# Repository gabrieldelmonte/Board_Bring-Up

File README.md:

# Board Bring-Up Project

A microcontroller-based embedded system project featuring real-time monitoring, alarm management, and multi-language support using the PIC18F4550 microcontroller.

## Project Overview

This project implements a comprehensive board bring-up system that combines multiple peripherals and sensors to create a monitoring and control system. The system features a state machine-based architecture with real-time clock functionality, analog sensor monitoring, alarm management, and a user-friendly LCD interface.

## Features

### Core Functionality
- **Real-Time Clock (RTC)**: DS1307-based timekeeping with hour, minute, and second setting
- **Analog Monitoring**: ADC-based sensor reading with configurable alarm thresholds
- **Alarm System**: Dual-level alarm monitoring (high/low thresholds) with visual indicators
- **Multi-Language Support**: Interface available in 6 different languages
- **State Machine Architecture**: Robust navigation system between different operational modes

### Hardware Peripherals
- **LCD Display**: 16-character display for system information and menus
- **LED Control**: Visual feedback and alarm indication system
- **Button Interface**: Navigation and parameter adjustment controls
- **I2C Communication**: For RTC and DAC communication
- **PWM Output**: Pulse width modulation for analog output control
- **Serial Communication**: UART interface for debugging and external communication
- **DAC Output**: MCP4725-based digital-to-analog conversion

### System States
- **Menu**: Main navigation interface
- **Alarm Configuration**: Set high and low alarm thresholds
- **Language Selection**: Choose from 6 available languages
- **Time Setting**: Configure hours, minutes, and seconds
- **Warning Mode**: Alert state when alarm conditions are triggered

## Hardware Requirements

### Microcontroller
- **PIC18F4550** microcontroller
- **20 MHz** crystal oscillator
- Power supply and basic support components

### Peripherals
- **DS1307** Real-Time Clock module
- **MCP4725** Digital-to-Analog Converter
- **16x2 LCD Display** with HD44780 controller
- **LEDs** for status indication
- **Push buttons** for user interface
- **Analog sensor** (connected to ADC channel 0)

### Development Tools
- MPLAB X IDE or compatible PIC development environment
- XC8 compiler for PIC18 family
- Programmer/debugger (PICkit, ICD, etc.)

## Project Structure

```
Board_Bring-Up/
├── src/
│   ├── main.c              # Main application entry point
│   └── code/
│       ├── ADC.c           # Analog-to-Digital Converter functions
│       ├── button.c        # Button handling and debouncing
│       ├── DAC_MCP4725.c   # MCP4725 DAC communication
│       ├── delay.c         # Timing and delay functions
│       ├── event.c         # Event handling and system events
│       ├── I2C.c           # I2C communication protocol
│       ├── LCD.c           # LCD display control functions
│       ├── LED.c           # LED control and patterns
│       ├── output.c        # Output formatting and display
│       ├── PWM.c           # Pulse Width Modulation control
│       ├── RTC_DS1307.c    # Real-Time Clock functions
│       ├── serial.c        # UART serial communication
│       ├── stateMachine.c  # Main state machine implementation
│       ├── variables.c     # Global variable management
│       └── headers/        # Header files for all modules
├── hardware/               # KiCad PCB design files
├── diagrams/               # System architecture diagrams
└── docs/                   # Project documentation
```

## Getting Started

### Prerequisites
1. MPLAB X IDE installed
2. XC8 compiler for PIC18 family
3. PIC programmer/debugger
4. Assembled hardware board or prototyping setup

### Building the Project
1. Clone this repository:
   ```bash
   git clone https://github.com/your-username/Board_Bring-Up.git
   cd Board_Bring-Up
   ```

2. Open the project in MPLAB X IDE

3. Configure the project settings:
   - Select PIC18F4550 as target device
   - Set XC8 as the compiler
   - Configure programmer/debugger

4. Build the project:
   - Click "Build" or use Ctrl+F11
   - Resolve any compilation errors

5. Program the microcontroller:
   - Connect your programmer
   - Click "Make and Program Device"

### Hardware Setup
1. Connect the LCD display to PORTD and control pins (RA2, RA3)
2. Wire the DS1307 RTC to the I2C bus (RC3/SCL, RC4/SDA)
3. Connect analog sensor to AN0 (RA0)
4. Wire push buttons for navigation
5. Connect LEDs for status indication
6. Ensure proper power supply (5V for PIC18F4550)

## Usage

### Navigation
- **Base Button**: Return to main menu from any state
- **Left/Right Buttons**: Navigate between menu options
- **Up/Down Buttons**: Adjust values in configuration modes

### Setting Alarms
1. Navigate to alarm configuration states
2. Use up/down buttons to adjust high and low thresholds
3. System will trigger warnings when sensor readings exceed limits

### Time Configuration
1. Access time setting modes through menu navigation
2. Adjust hours, minutes, and seconds individually
3. Changes are automatically saved to RTC

### Language Selection
- Navigate to language menu
- Choose from 6 available language options
- Interface will update to selected language

## Configuration

### System Parameters
Key configuration options in `defines.h`:
- `FREQ`: System frequency (20 MHz)
- `NUMBER_LANGUAGES`: Available languages (6)
- `MAX_ADC_VALUE`: Maximum ADC reading (1000)
- `MIN_ADC_VALUE`: Minimum ADC reading (0)

### Pin Assignments
- **LCD Data**: PORTD (RD0-RD7)
- **LCD Control**: RA2 (RS), RA3 (EN)
- **I2C**: RC3 (SCL), RC4 (SDA)
- **ADC Input**: RA0 (AN0)
- **LED Outputs**: Configurable in LED.c

## Additional Resources

- [PIC18F4550 Datasheet](https://www.microchip.com/en-us/product/PIC18F4550)
- [DS1307 RTC Datasheet](https://datasheets.maximintegrated.com/en/ds/DS1307.pdf)
- [MCP4725 DAC Datasheet](https://ww1.microchip.com/downloads/en/DeviceDoc/22039d.pdf)
- PCB design files are available in the `hardware/` directory

## License

This project is licensed under the terms specified in the LICENSE file.

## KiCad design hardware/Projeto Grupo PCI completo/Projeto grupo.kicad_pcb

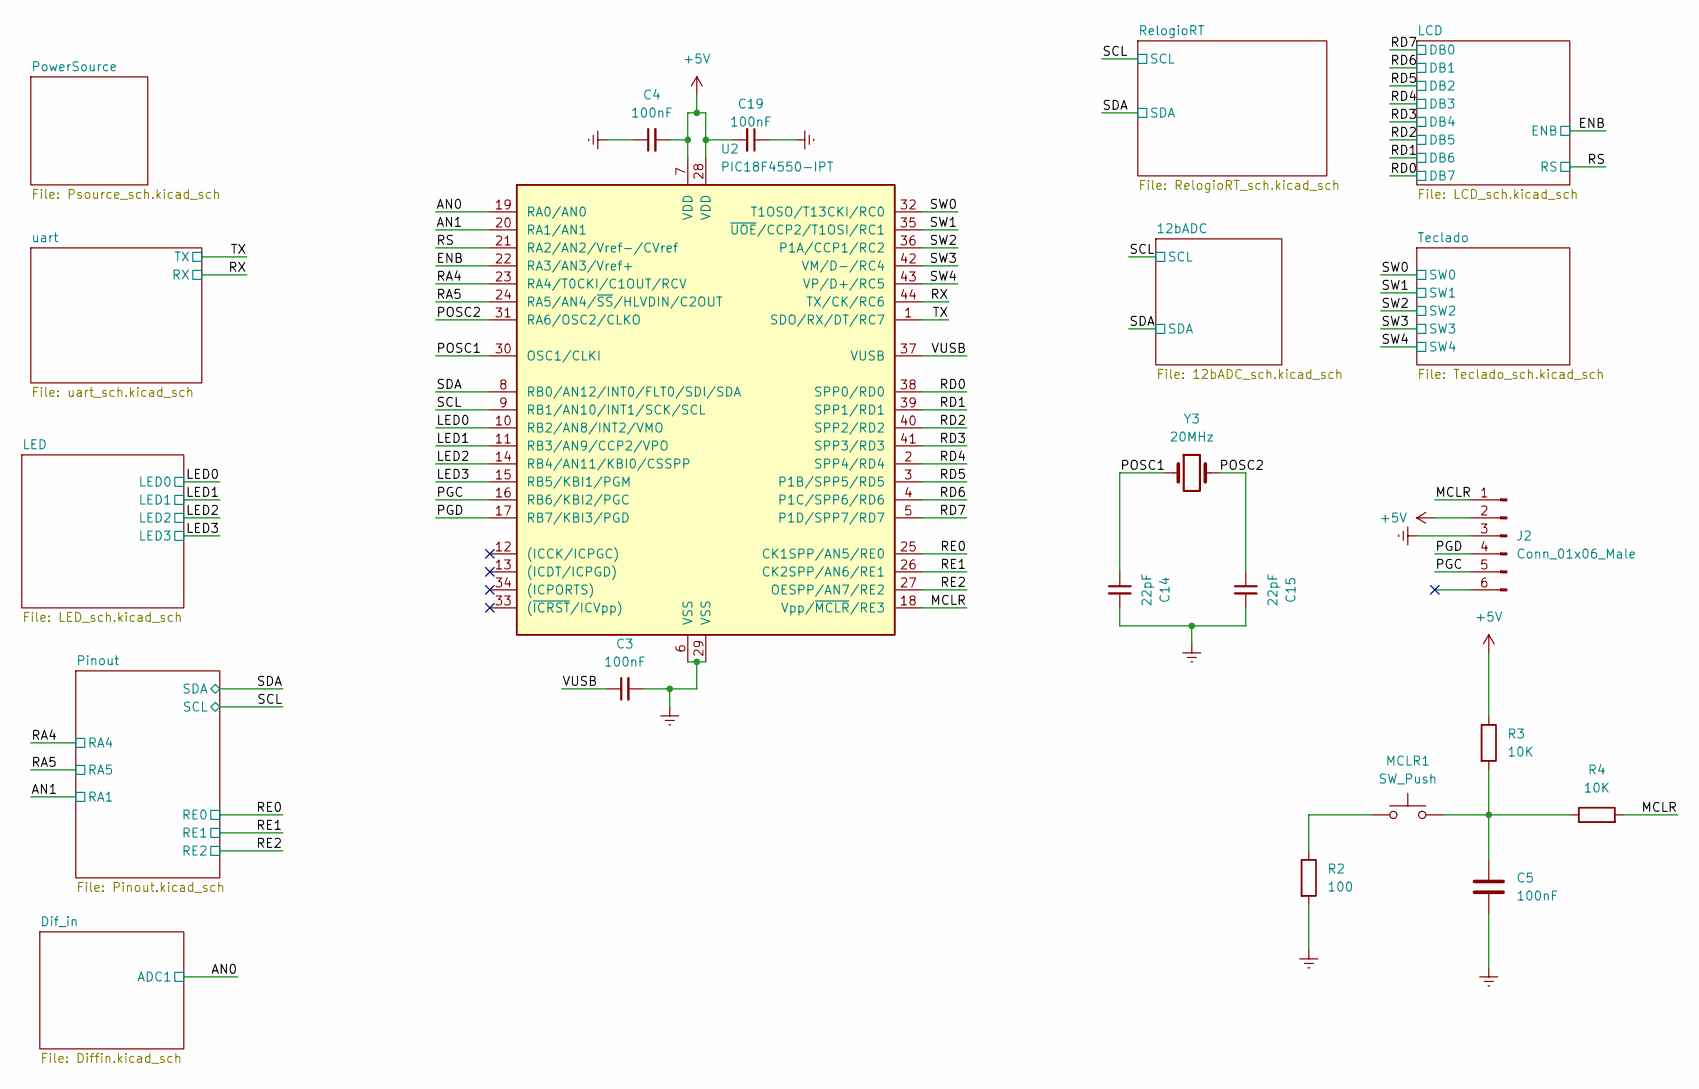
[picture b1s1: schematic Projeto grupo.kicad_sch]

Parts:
C3, C4, C5, C19: 100nF; C_0805_2012Metric
C14, C15: 22pF; C_0805_2012Metric
J2: Conn_01x06_Male; PinHeader_1x06_P2.54mm_Vertical
MCLR1: SW_Push; SW_PUSH_6mm
R2: 100; R_0805_2012Metric
R3, R4: 10K; R_0805_2012Metric
U2: PIC18F4550-IPT; TQFP-44_10x10mm_P0.8mm
Y3: 20MHz; Crystal_HC49-4H_Vertical

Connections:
+5V: C4.2, C19.2, J2.2, R3.1, U2.7 (VDD), U2.28 (VDD); also elsewhere on the board
/AN0: U2.19 (RA0/AN0); also elsewhere on the board
/AN1: U2.20 (RA1/AN1); also elsewhere on the board
/ENB: U2.22 (RA3/AN3/Vref+); also elsewhere on the board
/LED0: U2.10 (RB2/AN8/INT2/VMO); also elsewhere on the board
/LED1: U2.11 (RB3/AN9/CCP2/VPO); also elsewhere on the board
/LED2: U2.14 (RB4/AN11/KBI0/CSSPP); also elsewhere on the board
/LED3: U2.15 (RB5/KBI1/PGM); also elsewhere on the board
/MCLR: J2.1, R4.2, U2.18 (Vpp/~MCLR/RE3)
/PGC: J2.5, U2.16 (RB6/KBI2/PGC)
/PGD: J2.4, U2.17 (RB7/KBI3/PGD)
/POSC1: C14.1, U2.30 (OSC1/CLKI), Y3.1
/POSC2: C15.1, U2.31 (RA6/OSC2/CLKO), Y3.2
/RA4: U2.23 (RA4/T0CKI/C1OUT/RCV); also elsewhere on the board
/RA5: U2.24 (RA5/AN4/~SS/HLVDIN/C2OUT); also elsewhere on the board
/RD0: U2.38 (SPP0/RD0); also elsewhere on the board
/RD1: U2.39 (SPP1/RD1); also elsewhere on the board
/RD2: U2.40 (SPP2/RD2); also elsewhere on the board
/RD3: U2.41 (SPP3/RD3); also elsewhere on the board
/RD4: U2.2 (SPP4/RD4); also elsewhere on the board
/RD5: U2.3 (P1B/SPP5/RD5); also elsewhere on the board
/RD6: U2.4 (P1C/SPP6/RD6); also elsewhere on the board
/RD7: U2.5 (P1D/SPP7/RD7); also elsewhere on the board
/RE0: U2.25 (CK1SPP/AN5/RE0); also elsewhere on the board
/RE1: U2.26 (CK2SPP/AN6/RE1); also elsewhere on the board
/RE2: U2.27 (OESPP/AN7/RE2); also elsewhere on the board
/RS: U2.21 (RA2/AN2/Vref-/CVref); also elsewhere on the board
/RX: U2.44 (TX/CK/RC6); also elsewhere on the board
/SCL: U2.9 (RB1/AN10/INT1/SCK/SCL); also elsewhere on the board
/SDA: U2.8 (RB0/AN12/INT0/FLT0/SDI/SDA); also elsewhere on the board
/SW0: U2.32 (T1OSO/T13CKI/RC0); also elsewhere on the board
/SW1: U2.35 (~UOE/CCP2/T1OSI/RC1); also elsewhere on the board
/SW2: U2.36 (P1A/CCP1/RC2); also elsewhere on the board
/SW3: U2.42 (VM/D-/RC4); also elsewhere on the board
/SW4: U2.43 (VP/D+/RC5); also elsewhere on the board
/TX: U2.1 (SDO/RX/DT/RC7); also elsewhere on the board
/VUSB: C3.1, U2.37 (VUSB)
Earth: C3.2, C4.1, C5.2, C14.2, C15.2, C19.1, J2.3, R2.2, U2.6 (VSS), U2.29 (VSS); also elsewhere on the board
unnamed 39: C5.1, MCLR1.2, R3.2, R4.1; also elsewhere on the board
unnamed 60: MCLR1.1, R2.1; also elsewhere on the board

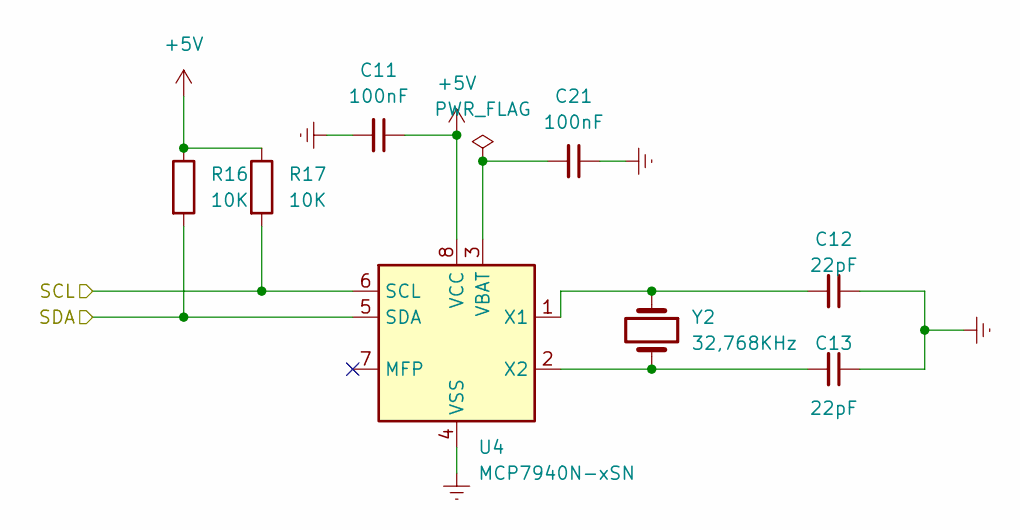
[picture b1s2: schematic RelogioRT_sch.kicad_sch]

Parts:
C11, C21: 100nF; C_0805_2012Metric
C12, C13: 22pF; C_0805_2012Metric
R16, R17: 10K; R_0805_2012Metric
U4: MCP7940N-xSN
Y2: 32,768KHz; AB38T32768KHZ

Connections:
+5V: C11.1, R16.1, R17.1, U4.8 (VCC); also elsewhere on the board
/SCL: R17.2, U4.6 (SCL); also elsewhere on the board
/SDA: R16.2, U4.5 (SDA); also elsewhere on the board
Earth: C11.2, C12.1, C13.1, C21.1, U4.4 (VSS); also elsewhere on the board
unnamed: C12.2, U4.1 (X1), Y2.1
unnamed: C13.2, U4.2 (X2), Y2.2
unnamed: C21.2, U4.3 (VBAT)

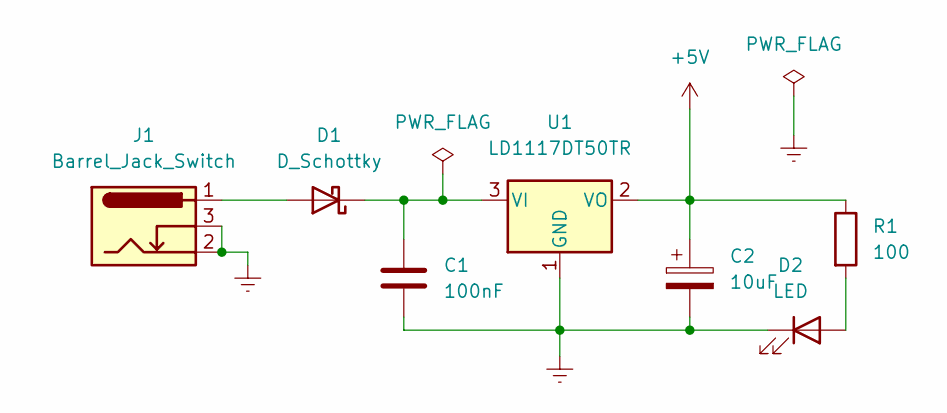
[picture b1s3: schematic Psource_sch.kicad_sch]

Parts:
C1: 100nF; C_0805_2012Metric
C2: 10uF; CP_EIA-3216-12_Kemet-S
D1: D_Schottky; D_SOD-123
D2: LED; LED_1206_3216Metric_Pad1.42x1.75mm_HandSolder
J1: Barrel_Jack_Switch; BarrelJack_Horizontal
R1: 100; R_0805_2012Metric
U1: LD1117DT50TR; ATPAK-2

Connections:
+5V: C2.1, R1.1, U1.2 (VO); also elsewhere on the board
Earth: C1.2, C2.2, D2.1 (K), J1.2, J1.3, U1.1 (GND); also elsewhere on the board
unnamed: C1.1, D1.1 (K), U1.3 (VI)
unnamed: D1.2 (A), J1.1
unnamed: D2.2 (A), R1.2

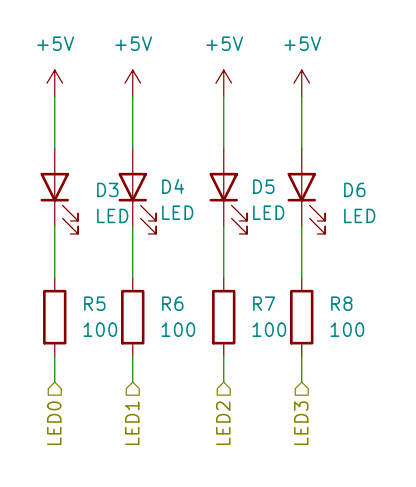
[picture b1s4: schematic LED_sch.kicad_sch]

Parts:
D3, D4, D5, D6: LED; LED_1206_3216Metric_Pad1.42x1.75mm_HandSolder
R5, R6, R7, R8: 100; R_0805_2012Metric

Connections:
+5V: D3.2 (A), D4.2 (A), D5.2 (A), D6.2 (A); also elsewhere on the board
/LED0: R5.2; also elsewhere on the board
/LED1: R6.2; also elsewhere on the board
/LED2: R7.2; also elsewhere on the board
/LED3: R8.2; also elsewhere on the board
unnamed: D3.1 (K), R5.1
unnamed: D4.1 (K), R6.1
unnamed: D5.1 (K), R7.1
unnamed: D6.1 (K), R8.1

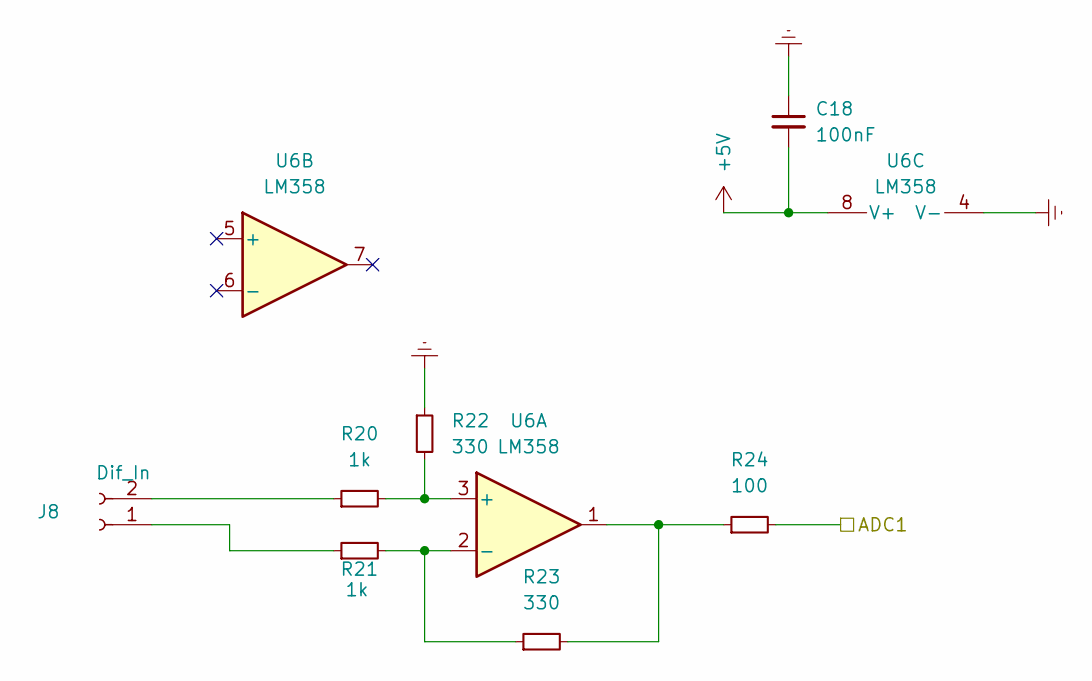
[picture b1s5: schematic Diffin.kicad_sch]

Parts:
C18: 100nF; C_0805_2012Metric
J8: Dif_In; On_Shore_Technology-OSTTA024163-0-0-MFG
R20, R21: 1k; R_0805_2012Metric
R22, R23: 330; R_0805_2012Metric
R24: 100; R_0805_2012Metric
U6: LM358

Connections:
+5V: C18.2, U6.8 (V+); also elsewhere on the board
/AN0: R24.2; also elsewhere on the board
Earth: C18.1, R22.1, U6.4 (V-); also elsewhere on the board
unnamed: J8.1, R21.1
unnamed: J8.2, R20.1
unnamed: R20.2, R22.2, U6.3 (+)
unnamed: R21.2, R23.1, U6.2 (-)
unnamed: R23.2, R24.1, U6.1

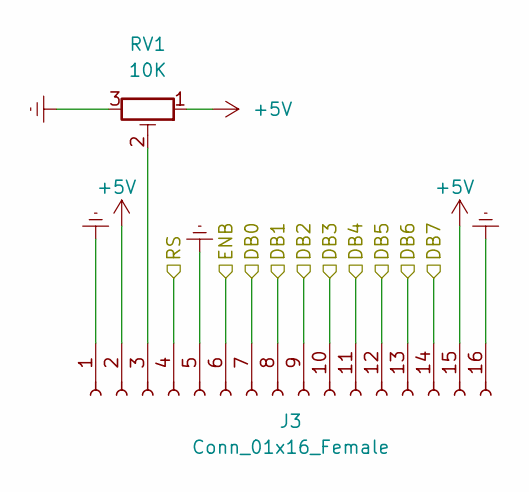
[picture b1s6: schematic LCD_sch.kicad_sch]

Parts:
J3: Conn_01x16_Female; PinSocket_1x16_P2.54mm_Vertical
RV1: 10K; Potentiometer_Bourns_3296W_Vertical

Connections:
+5V: J3.2, J3.15, RV1.1; also elsewhere on the board
/ENB: J3.6; also elsewhere on the board
/RD0: J3.14; also elsewhere on the board
/RD1: J3.13; also elsewhere on the board
/RD2: J3.12; also elsewhere on the board
/RD3: J3.11; also elsewhere on the board
/RD4: J3.10; also elsewhere on the board
/RD5: J3.9; also elsewhere on the board
/RD6: J3.8; also elsewhere on the board
/RD7: J3.7; also elsewhere on the board
/RS: J3.4; also elsewhere on the board
Earth: J3.1, J3.5, J3.16, RV1.3; also elsewhere on the board
unnamed: J3.3, RV1.2

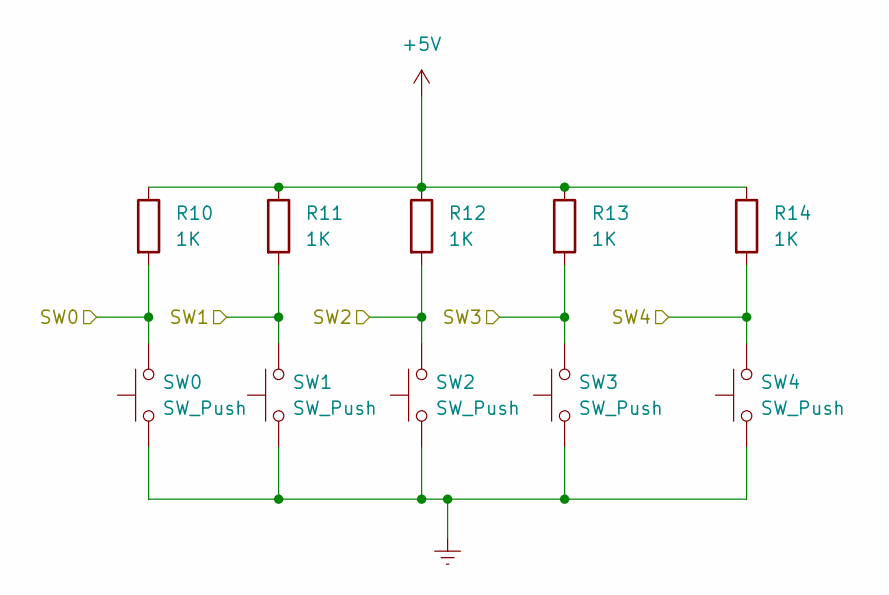
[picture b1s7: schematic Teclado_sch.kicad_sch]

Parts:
R10, R11, R12, R13, R14: 1K; R_0805_2012Metric
SW0, SW1, SW2, SW3, SW4: SW_Push; SW_PUSH_6mm

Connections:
+5V: R10.1, R11.1, R12.1, R13.1, R14.1; also elsewhere on the board
/SW0: R10.2, SW0.2; also elsewhere on the board
/SW1: R11.2, SW1.2; also elsewhere on the board
/SW2: R12.2, SW2.2; also elsewhere on the board
/SW3: R13.2, SW3.2; also elsewhere on the board
/SW4: R14.2, SW4.2; also elsewhere on the board
Earth: SW0.1, SW1.1, SW2.1, SW3.1, SW4.1; also elsewhere on the board

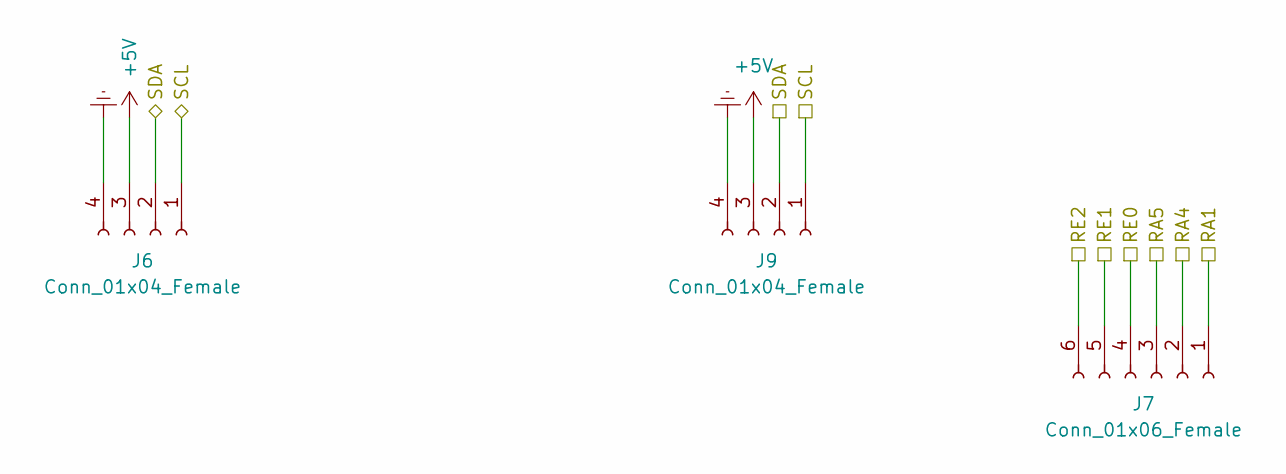
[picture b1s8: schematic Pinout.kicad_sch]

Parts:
J6, J9: Conn_01x04_Female; PinSocket_1x04_P2.54mm_Vertical
J7: Conn_01x06_Female; PinSocket_1x06_P2.54mm_Vertical

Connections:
+5V: J6.3, J9.3; also elsewhere on the board
/AN1: J7.1; also elsewhere on the board
/RA4: J7.2; also elsewhere on the board
/RA5: J7.3; also elsewhere on the board
/RE0: J7.4; also elsewhere on the board
/RE1: J7.5; also elsewhere on the board
/RE2: J7.6; also elsewhere on the board
/SCL: J6.1, J9.1; also elsewhere on the board
/SDA: J6.2, J9.2; also elsewhere on the board
Earth: J6.4, J9.4; also elsewhere on the board

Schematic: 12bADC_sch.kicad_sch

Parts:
C16: 100nF; C_0805_2012Metric
C17: 10uF; CP_EIA-3216-12_Kemet-S
J5: adcout; On_Shore_Technology-OSTTA024163-0-0-MFG
R15: 100; R_0805_2012Metric
U5: MCP4725A0T-E/CH; SOT-23-6

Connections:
+5V: C16.2, C17.1, U5.3 (VDD); also elsewhere on the board
/SCL: U5.5 (SCL); also elsewhere on the board
/SDA: U5.4 (SDA); also elsewhere on the board
Earth: C16.1, C17.2, J5.2, U5.2 (VSS), U5.6 (A0); also elsewhere on the board
unnamed: J5.1, R15.2
unnamed: R15.1, U5.1 (VOUT)

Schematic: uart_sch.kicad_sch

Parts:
C6, C7: 22pF; C_0805_2012Metric
C8, C9, C20: 100nF; C_0805_2012Metric
C10: 220nF; C_0805_2012Metric
J4: USB_A; USB_B_Lumberg_2411_02_Horizontal
R9: 10K; R_0805_2012Metric
U3: MCP2200-I-SO; SOIC-20W_7.5x12.8mm_P1.27mm
Y1: 12MHz; Crystal_HC49-4H_Vertical

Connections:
+5V: C9.2, R9.1, U3.1 (VDD); also elsewhere on the board
/RX: U3.12 (RX); also elsewhere on the board
/TX: U3.10 (TX); also elsewhere on the board
Earth: C6.2, C7.2, C8.1, C9.1, C10.2, C20.1, J4.4 (GND), U3.20 (VSS); also elsewhere on the board
unnamed: C6.1, U3.2 (OSC1), Y1.2
unnamed: C7.1, U3.3 (OSC2), Y1.1
unnamed: C8.2, R9.2, U3.4 (RST)
unnamed: C10.1, U3.17 (V_USB)
unnamed: C20.2, J4.1 (VBUS)
unnamed: J4.2 (D-), U3.18 (D-)
unnamed: J4.3 (D+), U3.19 (D+)

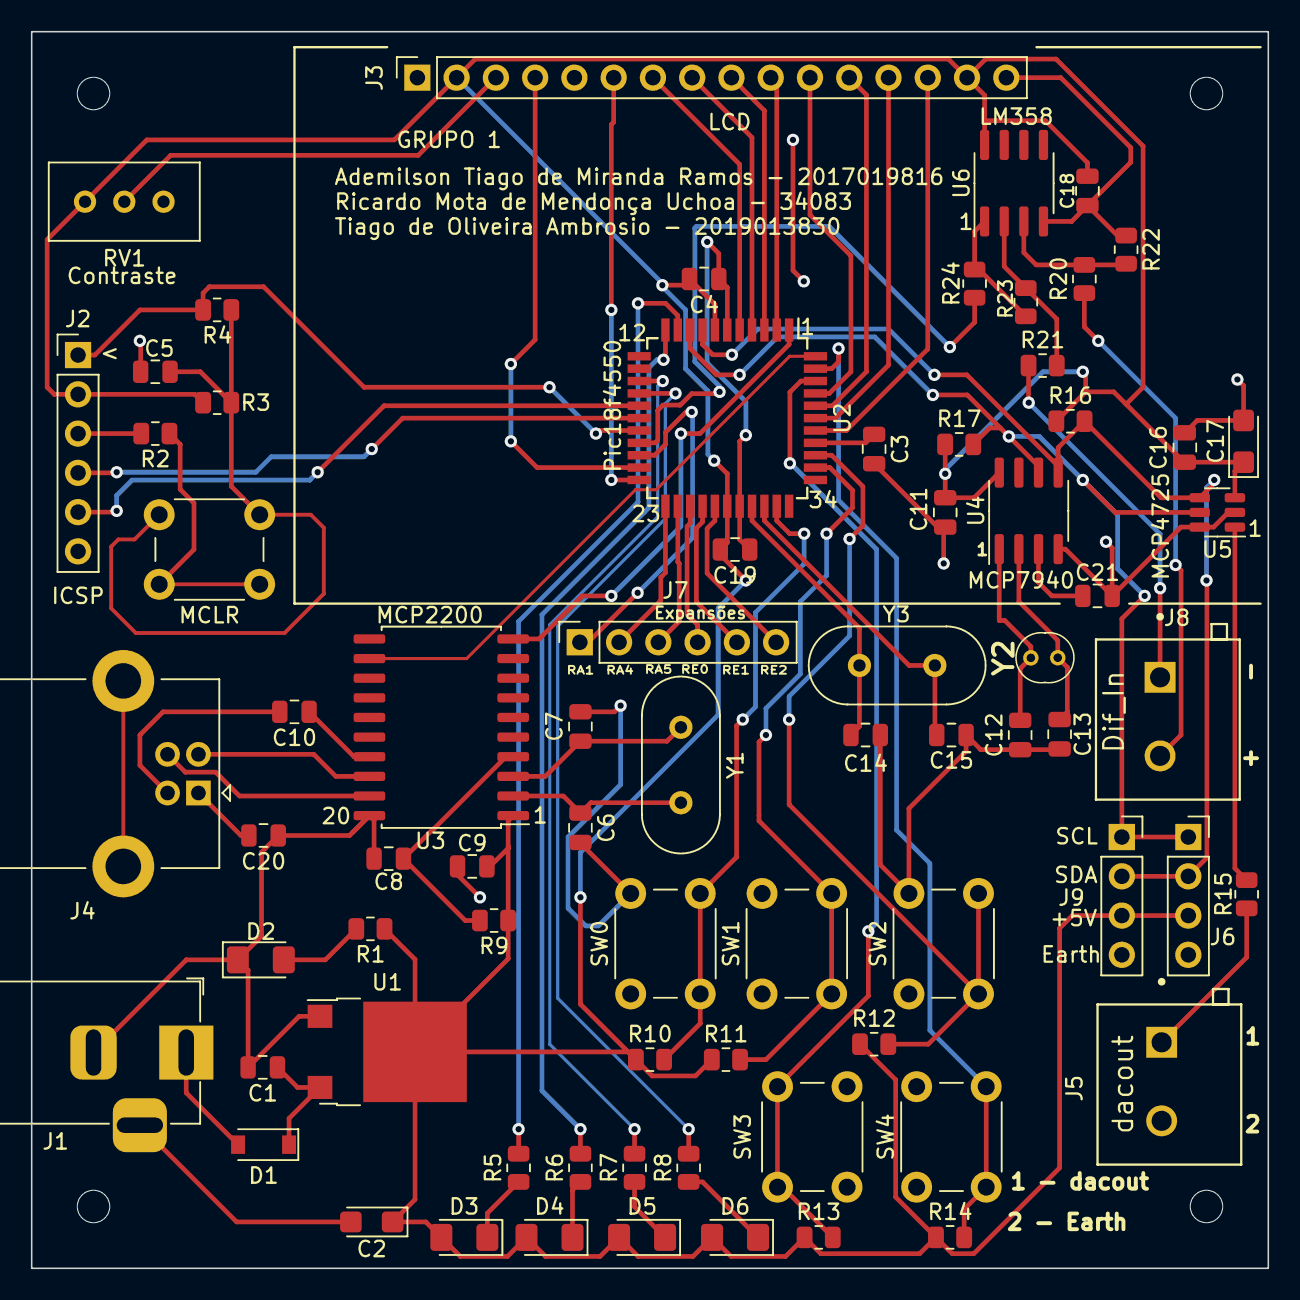
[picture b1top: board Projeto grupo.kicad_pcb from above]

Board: 2 copper layers, 80.0 x 80.0 mm, 74 parts (0 on the bottom side), 65 nets.

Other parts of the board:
MCLR: SW_Push; SW_PUSH_6mm

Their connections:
unnamed 39: MCLR.2; also elsewhere on the board
unnamed 60: MCLR.1; also elsewhere on the board

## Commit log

2025-07-27 project
